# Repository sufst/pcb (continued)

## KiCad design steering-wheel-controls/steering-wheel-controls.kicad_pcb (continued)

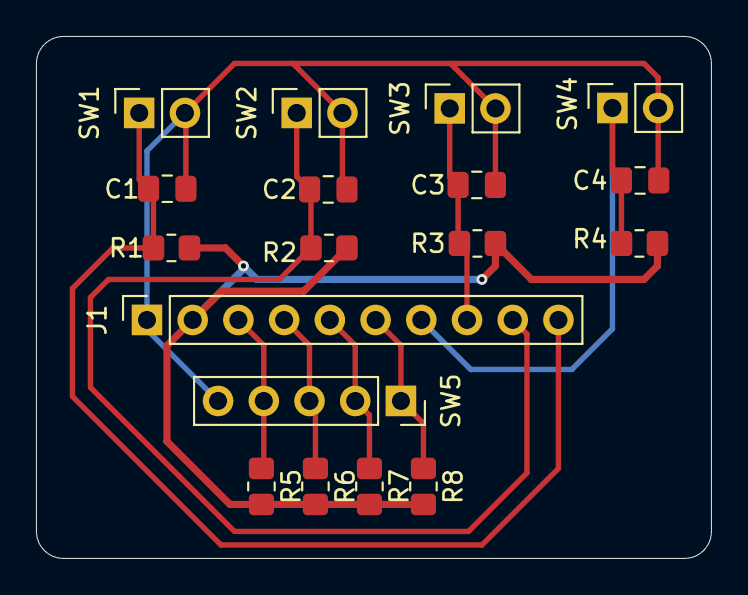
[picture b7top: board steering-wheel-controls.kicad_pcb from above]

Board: 2 copper layers, 37.5 x 29.0 mm, 18 parts (0 on the bottom side), 10 nets.
